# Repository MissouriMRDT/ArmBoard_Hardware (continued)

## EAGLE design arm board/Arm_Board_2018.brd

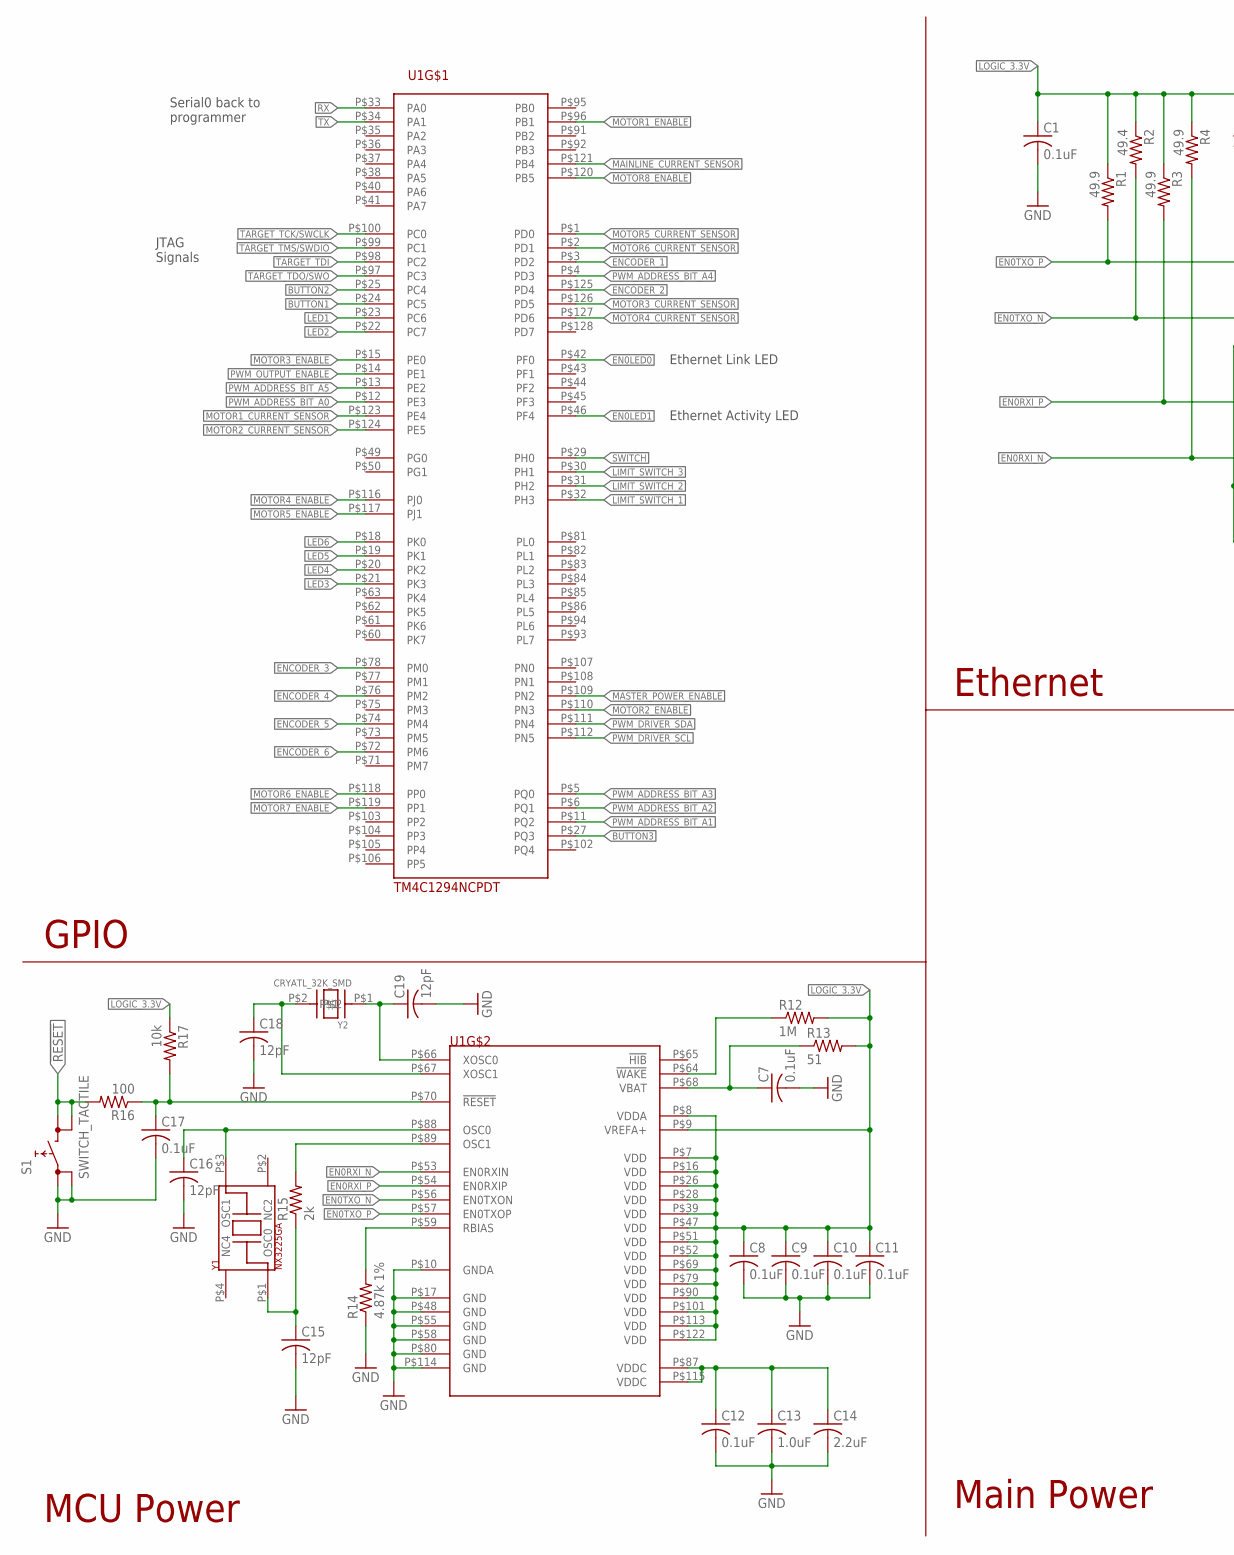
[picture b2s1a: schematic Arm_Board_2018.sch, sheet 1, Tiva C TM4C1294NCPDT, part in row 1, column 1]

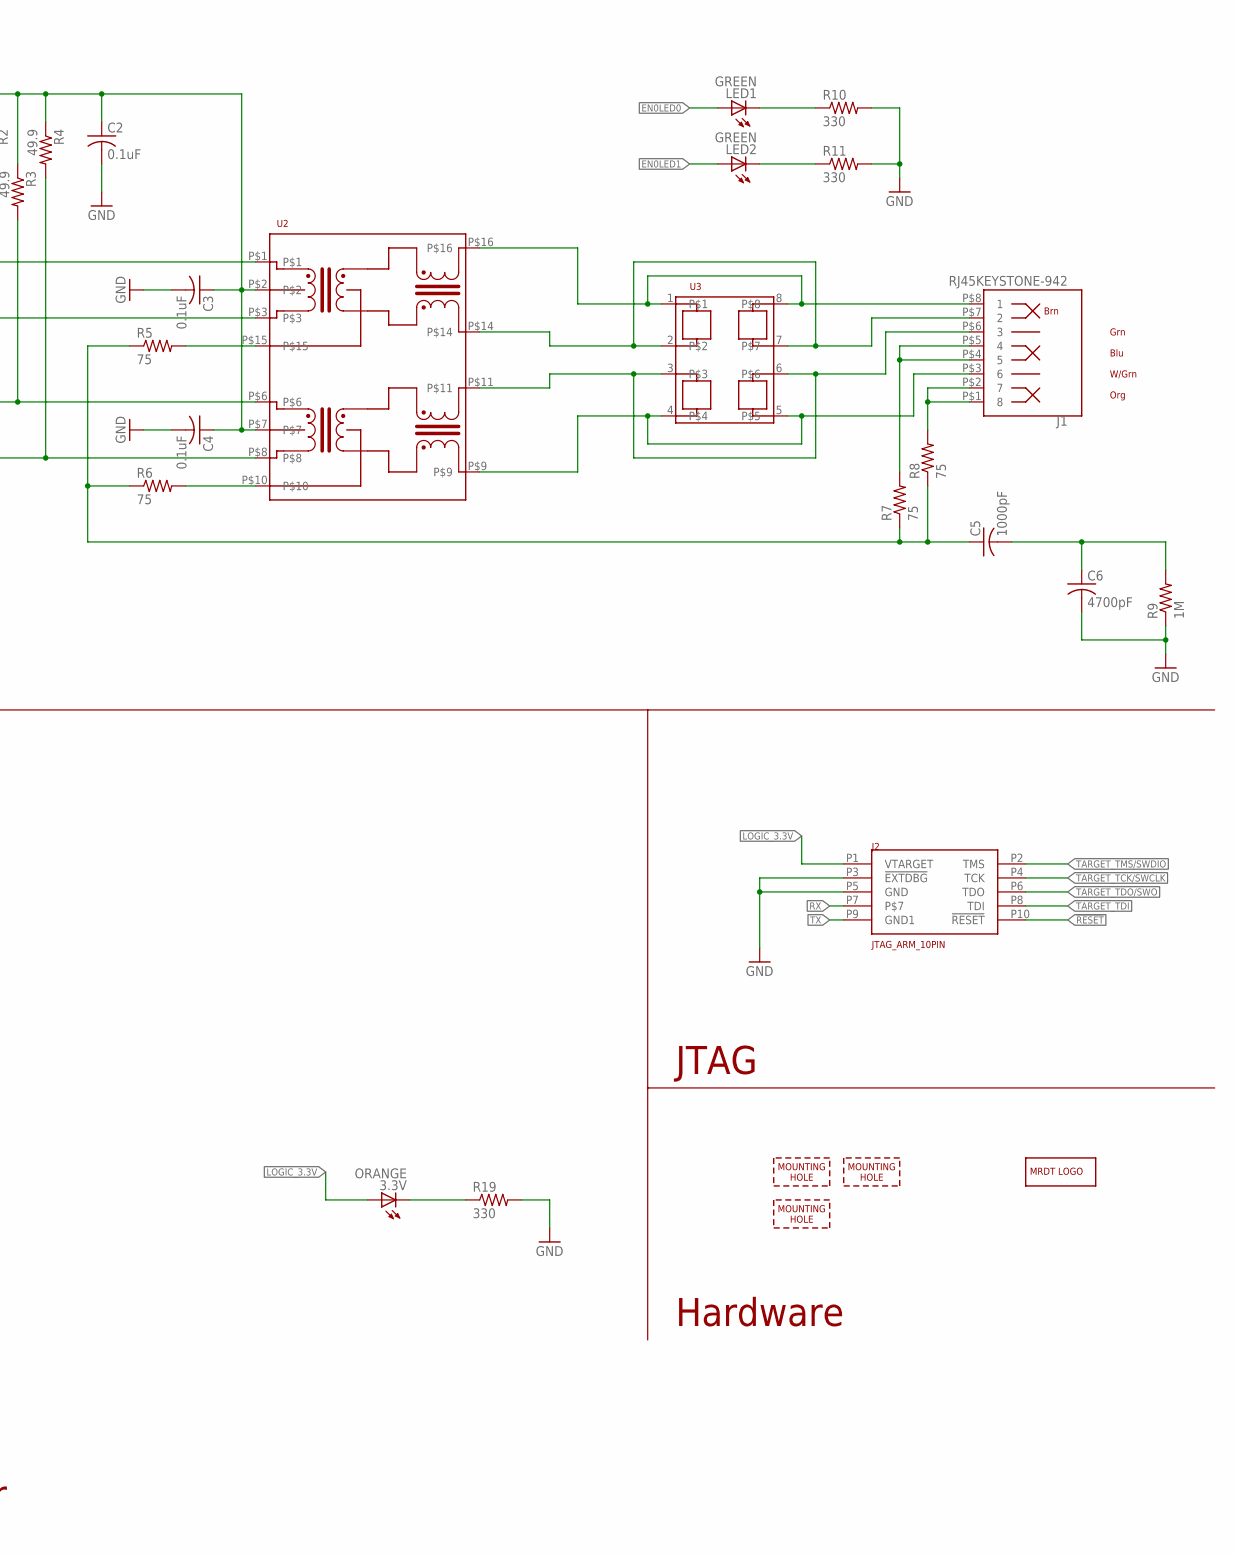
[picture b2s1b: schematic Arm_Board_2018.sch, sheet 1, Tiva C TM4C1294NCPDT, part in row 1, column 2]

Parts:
3.3V: ORANGE; CHIP-LED0603
C1, C2, C3, C4, C7, C8, C9, C10, C11, C12, C17: 0.1uF; C0603
C5: 1000pF; C0603
C6: 4700pF; C1206
C13: 1.0uF; C0603
C14: 2.2uF; C0603
C15, C16, C18, C19: 12pF; C0603
J1: RJ45KEYSTONE-942; KEYSTONE-942
J2: JTAG_ARM_10PIN; CON_2X5_50MIL
LED1, LED2: GREEN; CHIP-LED0603
R1, R3, R4: 49.9; R0603
R2: 49.4; R0603
R5, R6, R7, R8: 75; R0603
R9: 1M; R1206
R10, R11, R19: 330; R0603
R12: 1M; R0603
R13: 51; R0603
R14: 4.87k 1%; R0603
R15: 2k; R0603
R16: 100; R0603
R17: 10k; R0603
S1: SWITCH_TACTILE; SWITCH_6MM_6MM_TE_CON_SMD
U1: TM4C1294NCPDT; TQFP-128
U2: HX1198FNL
U3: SLVU2.8-4; SOIC8
U$1: MRDT_LOGO
U$2, U$3, U$4: MOUNTING_HOLE#6; #6_SCREW
Y1: NX3225GA; NDK3.2X2.5
Y2: CRYATL_32K_SMD; CRYSTAL_32K_SMD

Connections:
!RESET: J2.P10 (!RESET), R16.2, S1.P$3 (1), S1.P$4 (1)
BUTTON1: U1.P$24 (PC5); also elsewhere on the board
BUTTON2: U1.P$25 (PC4); also elsewhere on the board
BUTTON3: U1.P$27 (PQ3); also elsewhere on the board
EN0LED0: LED1.A, U1.P$42 (PF0)
EN0LED1: LED2.A, U1.P$46 (PF4)
EN0RXI_N: R4.2, U1.P$53 (EN0RXIN), U2.P$8
EN0RXI_P: R3.2, U1.P$54 (EN0RXIP), U2.P$6
EN0TXO_N: R2.2, U1.P$56 (EN0TXON), U2.P$3
EN0TXO_P: R1.2, U1.P$57 (EN0TXOP), U2.P$1
ENCODER_1: U1.P$3 (PD2); also elsewhere on the board
ENCODER_2: U1.P$125 (PD4); also elsewhere on the board
ENCODER_3: U1.P$78 (PM0); also elsewhere on the board
ENCODER_4: U1.P$76 (PM2); also elsewhere on the board
ENCODER_5: U1.P$74 (PM4); also elsewhere on the board
ENCODER_6: U1.P$72 (PM6); also elsewhere on the board
GND: C1.2, C2.2, C3.2, C4.2, C6.2, C7.2, C8.2, C9.2, C10.2, C11.2, C12.2, C13.2, C14.2, C15.2, C16.2, C17.2, C18.2, C19.2, J2.P3 (!EXTDBG), J2.P5 (GND), R9.1, R10.2, R11.2, R14.1, R19.2, S1.P$1 (0), S1.P$2 (0), U1.P$10 (GNDA), U1.P$17 (GND), U1.P$48 (GND), U1.P$55 (GND), U1.P$58 (GND), U1.P$80 (GND), U1.P$114 (GND); also elsewhere on the board
LED1: U1.P$23 (PC6); also elsewhere on the board
LED2: U1.P$22 (PC7); also elsewhere on the board
LED3: U1.P$21 (PK3); also elsewhere on the board
LED4: U1.P$20 (PK2); also elsewhere on the board
LED5: U1.P$19 (PK1); also elsewhere on the board
LED6: U1.P$18 (PK0); also elsewhere on the board
LIMIT_SWITCH_1: U1.P$32 (PH3); also elsewhere on the board
LIMIT_SWITCH_2: U1.P$31 (PH2); also elsewhere on the board
LIMIT_SWITCH_3: U1.P$30 (PH1); also elsewhere on the board
LOGIC_3.3V: 3.3V.A, C1.1, C2.1, C3.1, C4.1, C8.1, C9.1, C10.1, C11.1, J2.P1 (VTARGET), R1.1, R2.1, R3.1, R4.1, R12.2, R13.2, R17.1, U1.P$7 (VDD), U1.P$8 (VDDA), U1.P$9 (VREFA+), U1.P$16 (VDD), U1.P$26 (VDD), U1.P$28 (VDD), U1.P$39 (VDD), U1.P$47 (VDD), U1.P$51 (VDD), U1.P$52 (VDD), U1.P$69 (VDD), U1.P$79 (VDD), U1.P$90 (VDD), U1.P$101 (VDD), U1.P$113 (VDD), U1.P$122 (VDD), U2.P$2, U2.P$7; also elsewhere on the board
MAINLINE_CURRENT_SENSOR: U1.P$121 (PB4); also elsewhere on the board
MASTER_POWER_ENABLE: U1.P$109 (PN2); also elsewhere on the board
MOTOR1_CURRENT_SENSOR: U1.P$123 (PE4); also elsewhere on the board
MOTOR1_ENABLE: U1.P$96 (PB1); also elsewhere on the board
MOTOR2_CURRENT_SENSOR: U1.P$124 (PE5); also elsewhere on the board
MOTOR2_ENABLE: U1.P$110 (PN3); also elsewhere on the board
MOTOR3_CURRENT_SENSOR: U1.P$126 (PD5); also elsewhere on the board
MOTOR3_ENABLE: U1.P$15 (PE0); also elsewhere on the board
MOTOR4_CURRENT_SENSOR: U1.P$127 (PD6); also elsewhere on the board
MOTOR4_ENABLE: U1.P$116 (PJ0); also elsewhere on the board
MOTOR5_CURRENT_SENSOR: U1.P$1 (PD0); also elsewhere on the board
MOTOR5_ENABLE: U1.P$117 (PJ1); also elsewhere on the board
MOTOR6_CURRENT_SENSOR: U1.P$2 (PD1); also elsewhere on the board
MOTOR6_ENABLE: U1.P$118 (PP0); also elsewhere on the board
MOTOR7_ENABLE: U1.P$119 (PP1); also elsewhere on the board
MOTOR8_ENABLE: U1.P$120 (PB5); also elsewhere on the board
N_$1: R5.2, U2.P$15
N_$3: R6.2, U2.P$10
N_$4: J1.P$7 (2), U2.P$14, U3.2, U3.7
N_$5: J1.P$6 (3), U2.P$11, U3.3, U3.6
N_$6: J1.P$8 (1), U2.P$16, U3.1, U3.8
N_$7: J1.P$3 (6), U2.P$9, U3.4, U3.5
N_$8: LED2.C, R11.1
N_$9: LED1.C, R10.1
N_$10: C7.1, R13.1, U1.P$68 (VBAT)
N_$11: J1.P$4 (5), J1.P$5 (4), R7.2
N_$12: R12.1, U1.P$64 (!WAKE)
N_$13: J1.P$1 (8), J1.P$2 (7), R8.2
N_$14: C5.1, R5.1, R6.1, R7.1, R8.1
N_$15: C5.2, C6.1, R9.2
N_$16: C12.1, C13.1, C14.1, U1.P$87 (VDDC), U1.P$115 (VDDC)
N_$17: R15.2, U1.P$89 (OSC1)
N_$18: C16.1, U1.P$88 (OSC0), Y1.P$3 (OSC1)
N_$19: R14.2, U1.P$59 (RBIAS)
N_$20: C17.1, R16.1, R17.2, U1.P$70 (!RESET)
N_$21: C15.1, R15.1, Y1.P$1 (OSC0)
N_$22: C18.1, U1.P$67 (XOSC1), Y2.P$2
N_$23: C19.1, U1.P$66 (XOSC0), Y2.P$1
N_$26: 3.3V.C, R19.1
PWM_ADDRESS_BIT_A0: U1.P$12 (PE3)
PWM_ADDRESS_BIT_A1: U1.P$11 (PQ2)
PWM_ADDRESS_BIT_A2: U1.P$6 (PQ1)
PWM_ADDRESS_BIT_A3: U1.P$5 (PQ0)
PWM_ADDRESS_BIT_A4: U1.P$4 (PD3)
PWM_ADDRESS_BIT_A5: U1.P$13 (PE2)
PWM_DRIVER_SCL: U1.P$112 (PN5); also elsewhere on the board
PWM_DRIVER_SDA: U1.P$111 (PN4); also elsewhere on the board
PWM_OUTPUT_ENABLE: U1.P$14 (PE1); also elsewhere on the board
RX: J2.P7, U1.P$33 (PA0)
SWITCH: U1.P$29 (PH0); also elsewhere on the board
TARGET_TCK/SWCLK: J2.P4 (TCK), U1.P$100 (PC0)
TARGET_TDI: J2.P8 (TDI), U1.P$98 (PC2)
TARGET_TDO/SWO: J2.P6 (TDO), U1.P$97 (PC3)
TARGET_TMS/SWDIO: J2.P2 (TMS), U1.P$99 (PC1)
TX: J2.P9 (GND1), U1.P$34 (PA1)

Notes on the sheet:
Ethernet
GPIO
MCU Power
Main Power
JTAG
Hardware
Serial0 back to programmer
JTAG Signals
Ethernet Link LED
Ethernet Activity LED

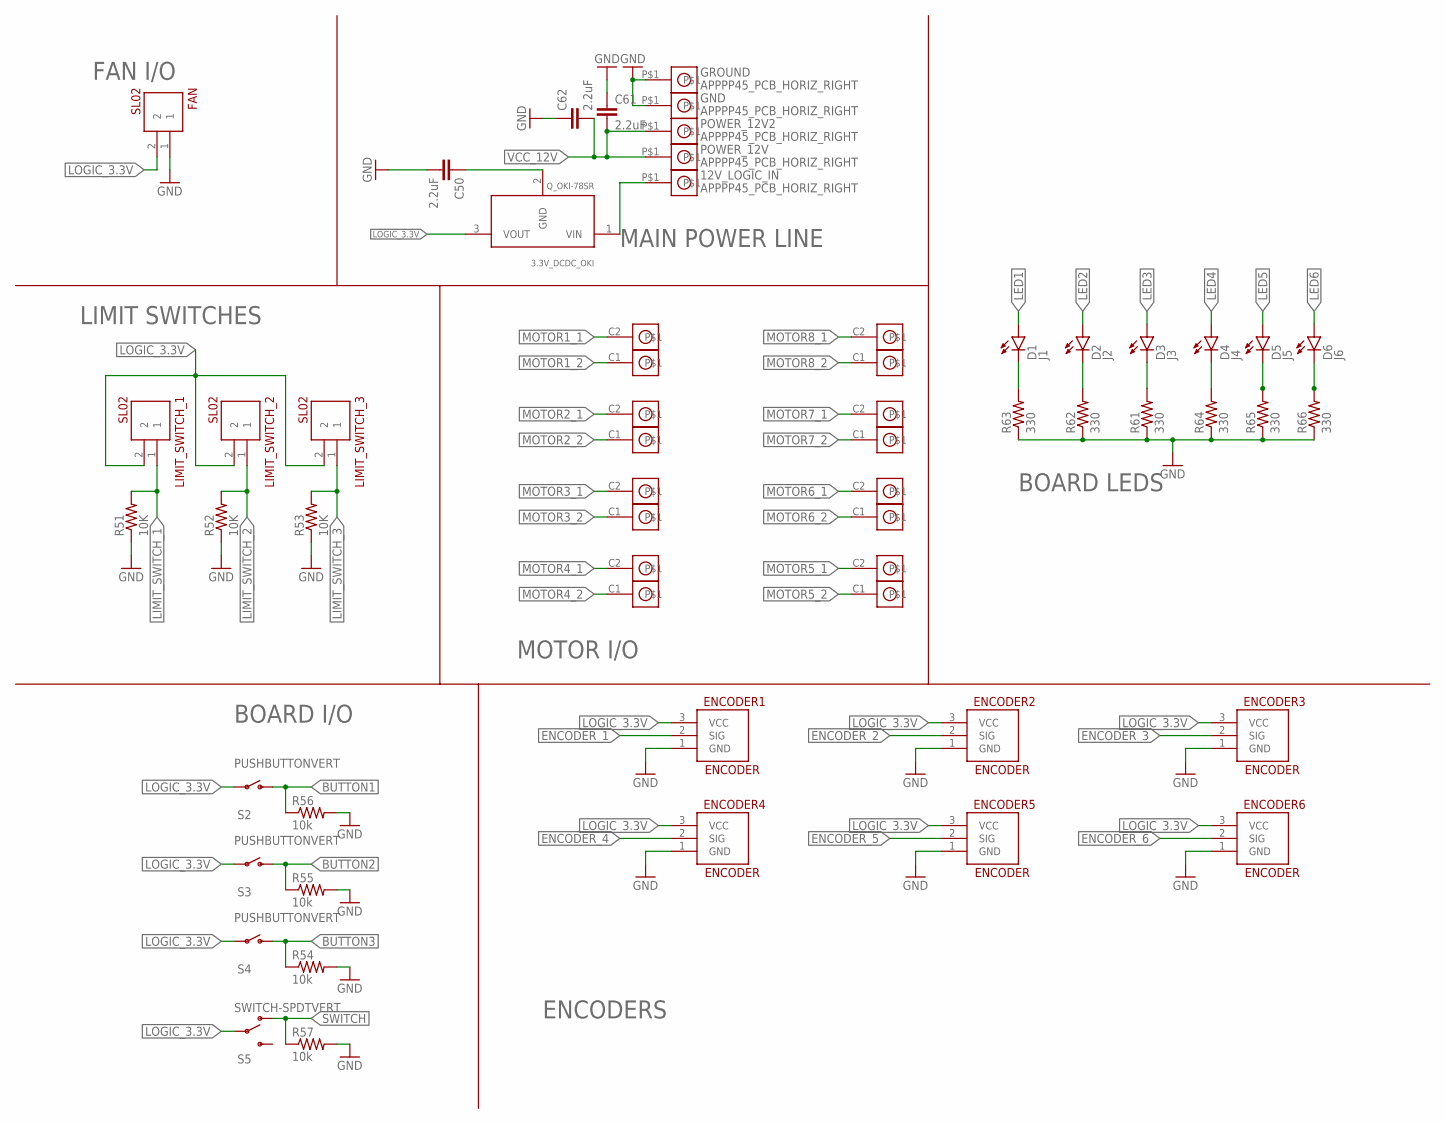
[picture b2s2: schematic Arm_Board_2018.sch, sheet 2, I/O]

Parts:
3.3V_DCDC_OKI: Q_OKI-78SR
12V_LOGIC_IN: APPPP45_PCB_HORIZ_RIGHT; APP45_PCB_HORIZ_RIGHT
C50: 2.2uF; 0603-CAP
C61, C62: 2.2uF; 1206
D1: J1; LED-0603
D2: J2; LED-0603
D3: J3; LED-0603
D4: J4; LED-0603
D5: J5; LED-0603
D6: J6; LED-0603
ENCODER1, ENCODER2, ENCODER3, ENCODER4, ENCODER5, ENCODER6: ENCODER; MOLEX-70543-0002
FAN: SL02; MOLEX-70543-0001
GND: APPPP45_PCB_HORIZ_RIGHT; APP45_PCB_HORIZ_RIGHT
GROUND: APPPP45_PCB_HORIZ_RIGHT; APP45_PCB_HORIZ_RIGHT
LIMIT_SWITCH_1, LIMIT_SWITCH_2, LIMIT_SWITCH_3: SL02; MOLEX-70543-0001
MOTOR1, MOTOR2, MOTOR3, MOTOR4, MOTOR5, MOTOR6, MOTOR7, MOTOR8: APP_2POS_CONFIGGENERAL_CONFIG; APP45_HORIZ_CONFIG
POWER_12V, POWER_12V2: APPPP45_PCB_HORIZ_RIGHT; APP45_PCB_HORIZ_RIGHT
R51, R52, R53: 10K; 0402-RES
R54, R55, R56, R57: 10k; 0402-RES
R61, R62, R63, R64, R65, R66: 330; 0402-RES
S2, S3, S4: PUSHBUTTONVERT; APEM-MJTP1243
S5: SWITCH-SPDTVERT; C&K-SS12D07VG4NSGAPA

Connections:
BUTTON1: R56.1, S2.P$2 (S); also elsewhere on the board
BUTTON2: R55.1, S3.P$2 (S); also elsewhere on the board
BUTTON3: R54.1, S4.P$2 (S); also elsewhere on the board
ENCODER_1: ENCODER1.2 (SIG); also elsewhere on the board
ENCODER_2: ENCODER2.2 (SIG); also elsewhere on the board
ENCODER_3: ENCODER3.2 (SIG); also elsewhere on the board
ENCODER_4: ENCODER4.2 (SIG); also elsewhere on the board
ENCODER_5: ENCODER5.2 (SIG); also elsewhere on the board
ENCODER_6: ENCODER6.2 (SIG); also elsewhere on the board
GND: C50.2, C61.1, C62.1, ENCODER1.1 (GND), ENCODER2.1 (GND), ENCODER3.1 (GND), ENCODER4.1 (GND), ENCODER5.1 (GND), ENCODER6.1 (GND), FAN.1, GND.P$1, GROUND.P$1, R51.1, R52.1, R53.1, R54.2, R55.2, R56.2, R57.2, R61.1, R62.1, R63.1, R64.1, R65.1, R66.1; also elsewhere on the board
LED1: D1.A; also elsewhere on the board
LED2: D2.A; also elsewhere on the board
LED3: D3.A; also elsewhere on the board
LED4: D4.A; also elsewhere on the board
LED5: D5.A; also elsewhere on the board
LED6: D6.A; also elsewhere on the board
LIMIT_SWITCH_1: LIMIT_SWITCH_1.1, R51.2; also elsewhere on the board
LIMIT_SWITCH_2: LIMIT_SWITCH_2.1, R52.2; also elsewhere on the board
LIMIT_SWITCH_3: LIMIT_SWITCH_3.1, R53.2; also elsewhere on the board
LOGIC_3.3V: 3.3V_DCDC_OKI.3 (VOUT), ENCODER1.3 (VCC), ENCODER2.3 (VCC), ENCODER3.3 (VCC), ENCODER4.3 (VCC), ENCODER5.3 (VCC), ENCODER6.3 (VCC), FAN.2, LIMIT_SWITCH_1.2, LIMIT_SWITCH_2.2, LIMIT_SWITCH_3.2, S2.P$1, S3.P$1, S4.P$1, S5.P$2; also elsewhere on the board
MOTOR1_1: MOTOR1.C2; also elsewhere on the board
MOTOR1_2: MOTOR1.C1; also elsewhere on the board
MOTOR2_1: MOTOR2.C2; also elsewhere on the board
MOTOR2_2: MOTOR2.C1; also elsewhere on the board
MOTOR3_1: MOTOR3.C2; also elsewhere on the board
MOTOR3_2: MOTOR3.C1; also elsewhere on the board
MOTOR4_1: MOTOR4.C2; also elsewhere on the board
MOTOR4_2: MOTOR4.C1; also elsewhere on the board
MOTOR5_1: MOTOR5.C2; also elsewhere on the board
MOTOR5_2: MOTOR5.C1; also elsewhere on the board
MOTOR6_1: MOTOR6.C2; also elsewhere on the board
MOTOR6_2: MOTOR6.C1; also elsewhere on the board
MOTOR7_1: MOTOR7.C2; also elsewhere on the board
MOTOR7_2: MOTOR7.C1; also elsewhere on the board
MOTOR8_1: MOTOR8.C2; also elsewhere on the board
MOTOR8_2: MOTOR8.C1; also elsewhere on the board
unnamed: 3.3V_DCDC_OKI.2 (GND), C50.1
unnamed: 3.3V_DCDC_OKI.1 (VIN), 12V_LOGIC_IN.P$1
unnamed: D1.C, R63.2
unnamed: D2.C, R62.2
unnamed: D6.C, R66.2
unnamed: D3.C, R61.2
unnamed: D4.C, R64.2
unnamed: D5.C, R65.2
SWITCH: R57.1, S5.P$3 (O); also elsewhere on the board
VCC_12V: C61.2, C62.2, POWER_12V.P$1, POWER_12V2.P$1; also elsewhere on the board

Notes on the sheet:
FAN I/O
MOTOR I/O
MAIN POWER LINE
LIMIT SWITCHES
ENCODERS
BOARD I/O
BOARD LEDS

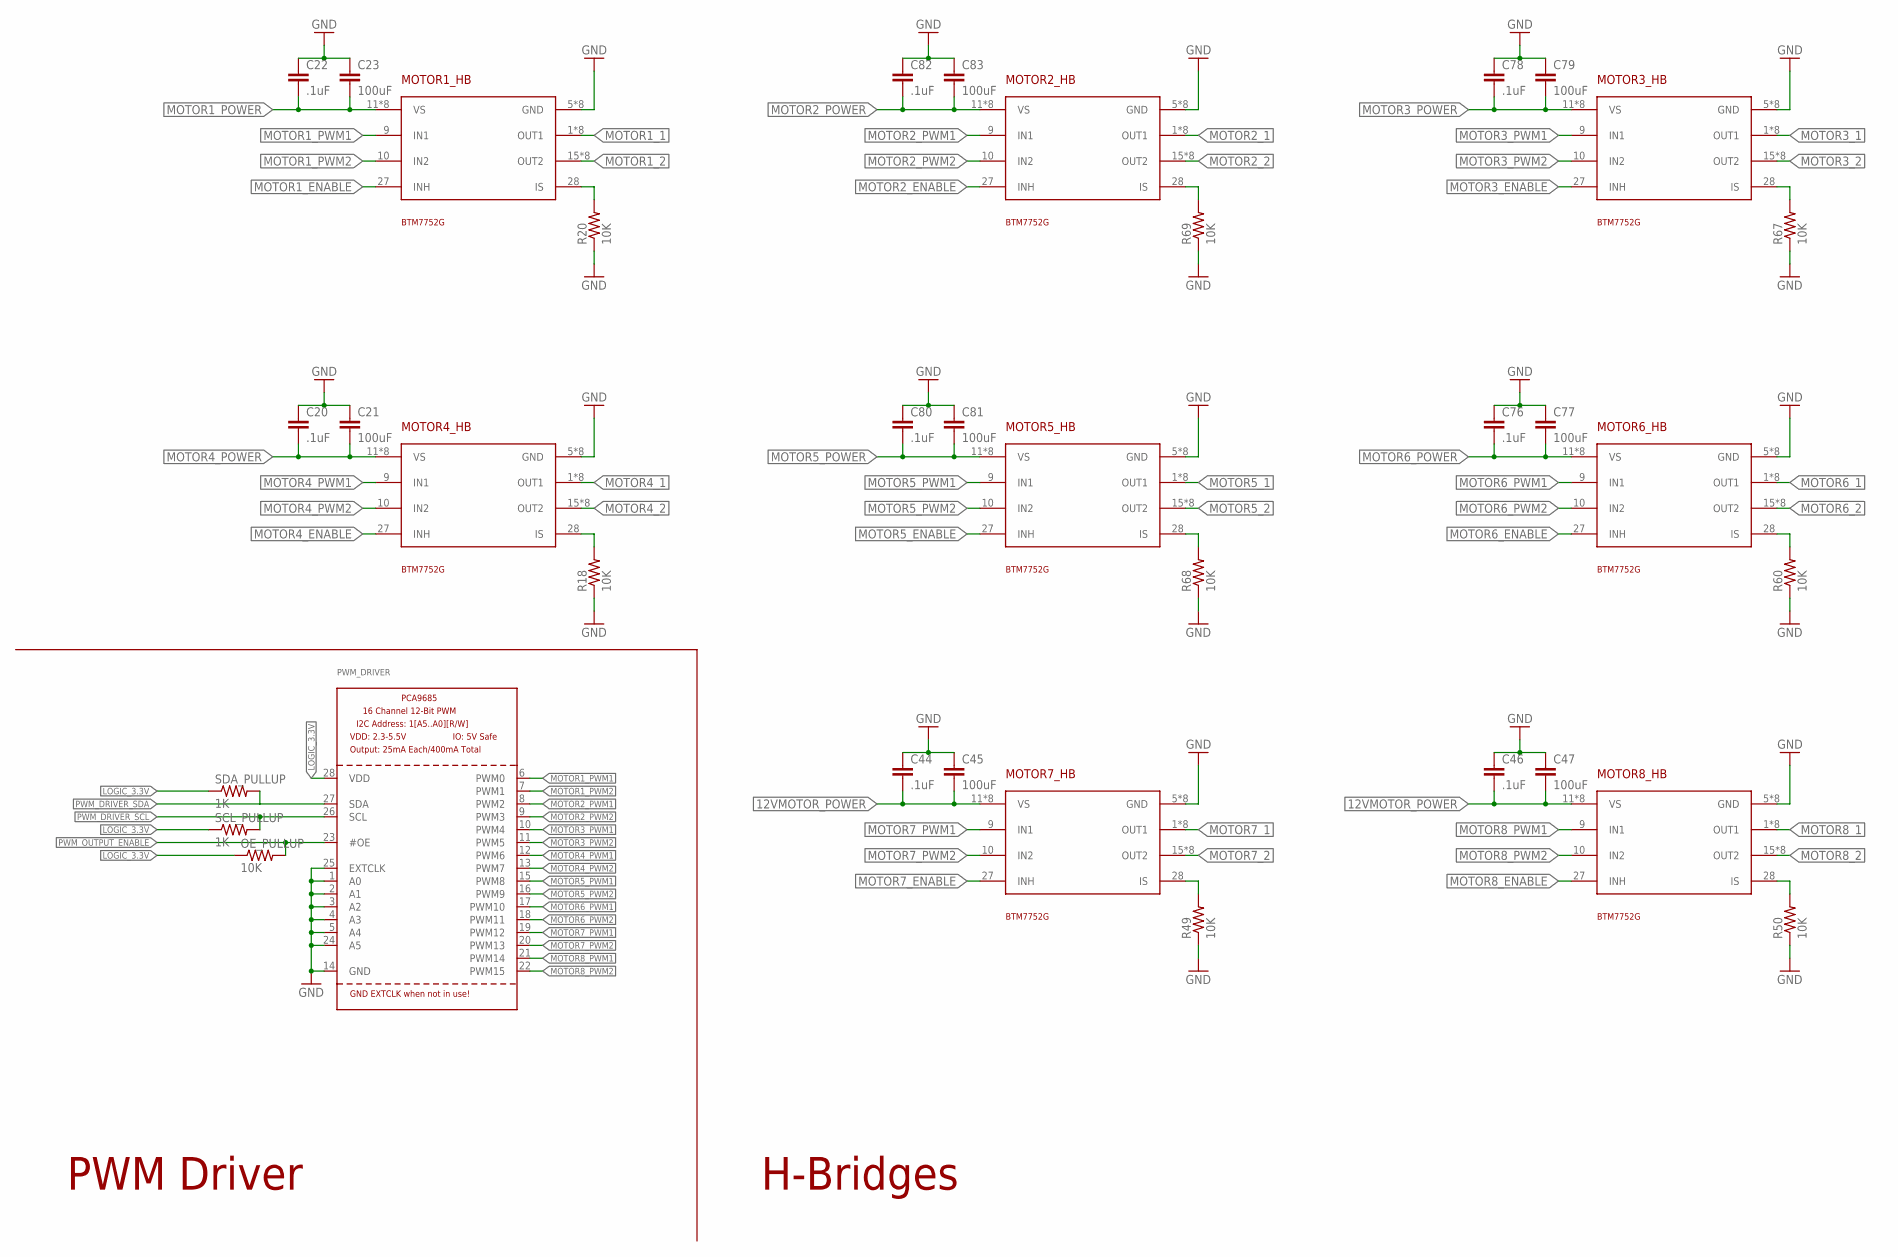
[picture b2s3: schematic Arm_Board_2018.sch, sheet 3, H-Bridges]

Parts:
C20, C22, C44, C46, C76, C78, C80, C82: .1uF; 0603-CAP
C21, C23, C45, C47, C77, C79, C81, C83: 100uF; 1210
MOTOR1_HB, MOTOR2_HB, MOTOR3_HB, MOTOR4_HB, MOTOR5_HB, MOTOR6_HB, MOTOR7_HB, MOTOR8_HB: BTM7752G; 36-BSSOP
OE_PULLUP: 10K; 0402-RES
PWM_DRIVER: PCA9685; TSSOP28
R18, R20, R49, R50, R60, R67, R68, R69: 10K; 0402-RES
SCL_PULLUP: 1K; 0402-RES
SDA_PULLUP: 1K; 0402-RES

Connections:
12VMOTOR_POWER: C44.2, C45.2, C46.2, C47.2, MOTOR7_HB.11 (VS), MOTOR7_HB.12 (VS), MOTOR7_HB.13 (VS), MOTOR7_HB.14 (VS), MOTOR7_HB.29 (VS), MOTOR7_HB.30 (VS), MOTOR7_HB.31 (VS), MOTOR7_HB.32 (VS), MOTOR8_HB.11 (VS), MOTOR8_HB.12 (VS), MOTOR8_HB.13 (VS), MOTOR8_HB.14 (VS), MOTOR8_HB.29 (VS), MOTOR8_HB.30 (VS), MOTOR8_HB.31 (VS), MOTOR8_HB.32 (VS); also elsewhere on the board
GND: C20.1, C21.1, C22.1, C23.1, C44.1, C45.1, C46.1, C47.1, C76.1, C77.1, C78.1, C79.1, C80.1, C81.1, C82.1, C83.1, MOTOR1_HB.5 (GND), MOTOR1_HB.6 (GND), MOTOR1_HB.7 (GND), MOTOR1_HB.8 (GND), MOTOR1_HB.23 (GND), MOTOR1_HB.24 (GND), MOTOR1_HB.25 (GND), MOTOR1_HB.26 (GND), MOTOR2_HB.5 (GND), MOTOR2_HB.6 (GND), MOTOR2_HB.7 (GND), MOTOR2_HB.8 (GND), MOTOR2_HB.23 (GND), MOTOR2_HB.24 (GND), MOTOR2_HB.25 (GND), MOTOR2_HB.26 (GND), MOTOR3_HB.5 (GND), MOTOR3_HB.6 (GND), MOTOR3_HB.7 (GND), MOTOR3_HB.8 (GND), MOTOR3_HB.23 (GND), MOTOR3_HB.24 (GND), MOTOR3_HB.25 (GND), MOTOR3_HB.26 (GND), MOTOR4_HB.5 (GND), MOTOR4_HB.6 (GND), MOTOR4_HB.7 (GND), MOTOR4_HB.8 (GND), MOTOR4_HB.23 (GND), MOTOR4_HB.24 (GND), MOTOR4_HB.25 (GND), MOTOR4_HB.26 (GND), MOTOR5_HB.5 (GND), MOTOR5_HB.6 (GND), MOTOR5_HB.7 (GND), MOTOR5_HB.8 (GND), MOTOR5_HB.23 (GND), MOTOR5_HB.24 (GND), MOTOR5_HB.25 (GND), MOTOR5_HB.26 (GND), MOTOR6_HB.5 (GND), MOTOR6_HB.6 (GND), MOTOR6_HB.7 (GND), MOTOR6_HB.8 (GND), MOTOR6_HB.23 (GND), MOTOR6_HB.24 (GND), MOTOR6_HB.25 (GND), MOTOR6_HB.26 (GND), MOTOR7_HB.5 (GND), MOTOR7_HB.6 (GND), MOTOR7_HB.7 (GND), MOTOR7_HB.8 (GND), MOTOR7_HB.23 (GND), MOTOR7_HB.24 (GND), MOTOR7_HB.25 (GND), MOTOR7_HB.26 (GND), MOTOR8_HB.5 (GND), MOTOR8_HB.6 (GND), MOTOR8_HB.7 (GND), MOTOR8_HB.8 (GND), MOTOR8_HB.23 (GND), MOTOR8_HB.24 (GND), MOTOR8_HB.25 (GND), MOTOR8_HB.26 (GND), PWM_DRIVER.1 (A0), PWM_DRIVER.2 (A1), PWM_DRIVER.3 (A2), PWM_DRIVER.4 (A3), PWM_DRIVER.5 (A4), PWM_DRIVER.14 (GND), PWM_DRIVER.24 (A5), PWM_DRIVER.25 (EXTCLK), R18.1, R20.1, R49.1, R50.1, R60.1, R67.1, R68.1, R69.1; also elsewhere on the board
LOGIC_3.3V: OE_PULLUP.1, PWM_DRIVER.28 (VDD), SCL_PULLUP.1, SDA_PULLUP.1; also elsewhere on the board
MOTOR1_1: MOTOR1_HB.1 (OUT1), MOTOR1_HB.2 (OUT1), MOTOR1_HB.3 (OUT1), MOTOR1_HB.4 (OUT1), MOTOR1_HB.33 (OUT1), MOTOR1_HB.34 (OUT1), MOTOR1_HB.35 (OUT1), MOTOR1_HB.36 (OUT1); also elsewhere on the board
MOTOR1_2: MOTOR1_HB.15 (OUT2), MOTOR1_HB.16 (OUT2), MOTOR1_HB.17 (OUT2), MOTOR1_HB.18 (OUT2), MOTOR1_HB.19 (OUT2), MOTOR1_HB.20 (OUT2), MOTOR1_HB.21 (OUT2), MOTOR1_HB.22 (OUT2); also elsewhere on the board
MOTOR1_ENABLE: MOTOR1_HB.27 (INH); also elsewhere on the board
MOTOR1_POWER: C22.2, C23.2, MOTOR1_HB.11 (VS), MOTOR1_HB.12 (VS), MOTOR1_HB.13 (VS), MOTOR1_HB.14 (VS), MOTOR1_HB.29 (VS), MOTOR1_HB.30 (VS), MOTOR1_HB.31 (VS), MOTOR1_HB.32 (VS); also elsewhere on the board
MOTOR1_PWM1: MOTOR1_HB.9 (IN1), PWM_DRIVER.6 (PWM0)
MOTOR1_PWM2: MOTOR1_HB.10 (IN2), PWM_DRIVER.7 (PWM1)
MOTOR2_1: MOTOR2_HB.1 (OUT1), MOTOR2_HB.2 (OUT1), MOTOR2_HB.3 (OUT1), MOTOR2_HB.4 (OUT1), MOTOR2_HB.33 (OUT1), MOTOR2_HB.34 (OUT1), MOTOR2_HB.35 (OUT1), MOTOR2_HB.36 (OUT1); also elsewhere on the board
MOTOR2_2: MOTOR2_HB.15 (OUT2), MOTOR2_HB.16 (OUT2), MOTOR2_HB.17 (OUT2), MOTOR2_HB.18 (OUT2), MOTOR2_HB.19 (OUT2), MOTOR2_HB.20 (OUT2), MOTOR2_HB.21 (OUT2), MOTOR2_HB.22 (OUT2); also elsewhere on the board
MOTOR2_ENABLE: MOTOR2_HB.27 (INH); also elsewhere on the board
MOTOR2_POWER: C82.2, C83.2, MOTOR2_HB.11 (VS), MOTOR2_HB.12 (VS), MOTOR2_HB.13 (VS), MOTOR2_HB.14 (VS), MOTOR2_HB.29 (VS), MOTOR2_HB.30 (VS), MOTOR2_HB.31 (VS), MOTOR2_HB.32 (VS); also elsewhere on the board
MOTOR2_PWM1: MOTOR2_HB.9 (IN1), PWM_DRIVER.8 (PWM2)
MOTOR2_PWM2: MOTOR2_HB.10 (IN2), PWM_DRIVER.9 (PWM3)
MOTOR3_1: MOTOR3_HB.1 (OUT1), MOTOR3_HB.2 (OUT1), MOTOR3_HB.3 (OUT1), MOTOR3_HB.4 (OUT1), MOTOR3_HB.33 (OUT1), MOTOR3_HB.34 (OUT1), MOTOR3_HB.35 (OUT1), MOTOR3_HB.36 (OUT1); also elsewhere on the board
MOTOR3_2: MOTOR3_HB.15 (OUT2), MOTOR3_HB.16 (OUT2), MOTOR3_HB.17 (OUT2), MOTOR3_HB.18 (OUT2), MOTOR3_HB.19 (OUT2), MOTOR3_HB.20 (OUT2), MOTOR3_HB.21 (OUT2), MOTOR3_HB.22 (OUT2); also elsewhere on the board
MOTOR3_ENABLE: MOTOR3_HB.27 (INH); also elsewhere on the board
MOTOR3_POWER: C78.2, C79.2, MOTOR3_HB.11 (VS), MOTOR3_HB.12 (VS), MOTOR3_HB.13 (VS), MOTOR3_HB.14 (VS), MOTOR3_HB.29 (VS), MOTOR3_HB.30 (VS), MOTOR3_HB.31 (VS), MOTOR3_HB.32 (VS); also elsewhere on the board
MOTOR3_PWM1: MOTOR3_HB.9 (IN1), PWM_DRIVER.10 (PWM4)
MOTOR3_PWM2: MOTOR3_HB.10 (IN2), PWM_DRIVER.11 (PWM5)
MOTOR4_1: MOTOR4_HB.1 (OUT1), MOTOR4_HB.2 (OUT1), MOTOR4_HB.3 (OUT1), MOTOR4_HB.4 (OUT1), MOTOR4_HB.33 (OUT1), MOTOR4_HB.34 (OUT1), MOTOR4_HB.35 (OUT1), MOTOR4_HB.36 (OUT1); also elsewhere on the board
MOTOR4_2: MOTOR4_HB.15 (OUT2), MOTOR4_HB.16 (OUT2), MOTOR4_HB.17 (OUT2), MOTOR4_HB.18 (OUT2), MOTOR4_HB.19 (OUT2), MOTOR4_HB.20 (OUT2), MOTOR4_HB.21 (OUT2), MOTOR4_HB.22 (OUT2); also elsewhere on the board
MOTOR4_ENABLE: MOTOR4_HB.27 (INH); also elsewhere on the board
MOTOR4_POWER: C20.2, C21.2, MOTOR4_HB.11 (VS), MOTOR4_HB.12 (VS), MOTOR4_HB.13 (VS), MOTOR4_HB.14 (VS), MOTOR4_HB.29 (VS), MOTOR4_HB.30 (VS), MOTOR4_HB.31 (VS), MOTOR4_HB.32 (VS); also elsewhere on the board
MOTOR4_PWM1: MOTOR4_HB.9 (IN1), PWM_DRIVER.12 (PWM6)
MOTOR4_PWM2: MOTOR4_HB.10 (IN2), PWM_DRIVER.13 (PWM7)
MOTOR5_1: MOTOR5_HB.1 (OUT1), MOTOR5_HB.2 (OUT1), MOTOR5_HB.3 (OUT1), MOTOR5_HB.4 (OUT1), MOTOR5_HB.33 (OUT1), MOTOR5_HB.34 (OUT1), MOTOR5_HB.35 (OUT1), MOTOR5_HB.36 (OUT1); also elsewhere on the board
MOTOR5_2: MOTOR5_HB.15 (OUT2), MOTOR5_HB.16 (OUT2), MOTOR5_HB.17 (OUT2), MOTOR5_HB.18 (OUT2), MOTOR5_HB.19 (OUT2), MOTOR5_HB.20 (OUT2), MOTOR5_HB.21 (OUT2), MOTOR5_HB.22 (OUT2); also elsewhere on the board
MOTOR5_ENABLE: MOTOR5_HB.27 (INH); also elsewhere on the board
MOTOR5_POWER: C80.2, C81.2, MOTOR5_HB.11 (VS), MOTOR5_HB.12 (VS), MOTOR5_HB.13 (VS), MOTOR5_HB.14 (VS), MOTOR5_HB.29 (VS), MOTOR5_HB.30 (VS), MOTOR5_HB.31 (VS), MOTOR5_HB.32 (VS); also elsewhere on the board
MOTOR5_PWM1: MOTOR5_HB.9 (IN1), PWM_DRIVER.15 (PWM8)
MOTOR5_PWM2: MOTOR5_HB.10 (IN2), PWM_DRIVER.16 (PWM9)
MOTOR6_1: MOTOR6_HB.1 (OUT1), MOTOR6_HB.2 (OUT1), MOTOR6_HB.3 (OUT1), MOTOR6_HB.4 (OUT1), MOTOR6_HB.33 (OUT1), MOTOR6_HB.34 (OUT1), MOTOR6_HB.35 (OUT1), MOTOR6_HB.36 (OUT1); also elsewhere on the board
MOTOR6_2: MOTOR6_HB.15 (OUT2), MOTOR6_HB.16 (OUT2), MOTOR6_HB.17 (OUT2), MOTOR6_HB.18 (OUT2), MOTOR6_HB.19 (OUT2), MOTOR6_HB.20 (OUT2), MOTOR6_HB.21 (OUT2), MOTOR6_HB.22 (OUT2); also elsewhere on the board
MOTOR6_ENABLE: MOTOR6_HB.27 (INH); also elsewhere on the board
MOTOR6_POWER: C76.2, C77.2, MOTOR6_HB.11 (VS), MOTOR6_HB.12 (VS), MOTOR6_HB.13 (VS), MOTOR6_HB.14 (VS), MOTOR6_HB.29 (VS), MOTOR6_HB.30 (VS), MOTOR6_HB.31 (VS), MOTOR6_HB.32 (VS); also elsewhere on the board
MOTOR6_PWM1: MOTOR6_HB.9 (IN1), PWM_DRIVER.17 (PWM10)
MOTOR6_PWM2: MOTOR6_HB.10 (IN2), PWM_DRIVER.18 (PWM11)
MOTOR7_1: MOTOR7_HB.1 (OUT1), MOTOR7_HB.2 (OUT1), MOTOR7_HB.3 (OUT1), MOTOR7_HB.4 (OUT1), MOTOR7_HB.33 (OUT1), MOTOR7_HB.34 (OUT1), MOTOR7_HB.35 (OUT1), MOTOR7_HB.36 (OUT1); also elsewhere on the board
MOTOR7_2: MOTOR7_HB.15 (OUT2), MOTOR7_HB.16 (OUT2), MOTOR7_HB.17 (OUT2), MOTOR7_HB.18 (OUT2), MOTOR7_HB.19 (OUT2), MOTOR7_HB.20 (OUT2), MOTOR7_HB.21 (OUT2), MOTOR7_HB.22 (OUT2); also elsewhere on the board
MOTOR7_ENABLE: MOTOR7_HB.27 (INH); also elsewhere on the board
MOTOR7_PWM1: MOTOR7_HB.9 (IN1), PWM_DRIVER.19 (PWM12)
MOTOR7_PWM2: MOTOR7_HB.10 (IN2), PWM_DRIVER.20 (PWM13)
MOTOR8_1: MOTOR8_HB.1 (OUT1), MOTOR8_HB.2 (OUT1), MOTOR8_HB.3 (OUT1), MOTOR8_HB.4 (OUT1), MOTOR8_HB.33 (OUT1), MOTOR8_HB.34 (OUT1), MOTOR8_HB.35 (OUT1), MOTOR8_HB.36 (OUT1); also elsewhere on the board
MOTOR8_2: MOTOR8_HB.15 (OUT2), MOTOR8_HB.16 (OUT2), MOTOR8_HB.17 (OUT2), MOTOR8_HB.18 (OUT2), MOTOR8_HB.19 (OUT2), MOTOR8_HB.20 (OUT2), MOTOR8_HB.21 (OUT2), MOTOR8_HB.22 (OUT2); also elsewhere on the board
MOTOR8_ENABLE: MOTOR8_HB.27 (INH); also elsewhere on the board
MOTOR8_PWM1: MOTOR8_HB.9 (IN1), PWM_DRIVER.21 (PWM14)
MOTOR8_PWM2: MOTOR8_HB.10 (IN2), PWM_DRIVER.22 (PWM15)
unnamed: MOTOR4_HB.28 (IS), R18.2
unnamed: MOTOR1_HB.28 (IS), R20.2
unnamed: MOTOR6_HB.28 (IS), R60.2
unnamed: MOTOR3_HB.28 (IS), R67.2
unnamed: MOTOR8_HB.28 (IS), R50.2
unnamed: MOTOR7_HB.28 (IS), R49.2
unnamed: MOTOR5_HB.28 (IS), R68.2
unnamed: MOTOR2_HB.28 (IS), R69.2
PWM_DRIVER_SCL: PWM_DRIVER.26 (SCL), SCL_PULLUP.2; also elsewhere on the board
PWM_DRIVER_SDA: PWM_DRIVER.27 (SDA), SDA_PULLUP.2; also elsewhere on the board
PWM_OUTPUT_ENABLE: OE_PULLUP.2, PWM_DRIVER.23 (#OE); also elsewhere on the board

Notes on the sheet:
PWM Driver
H-Bridges

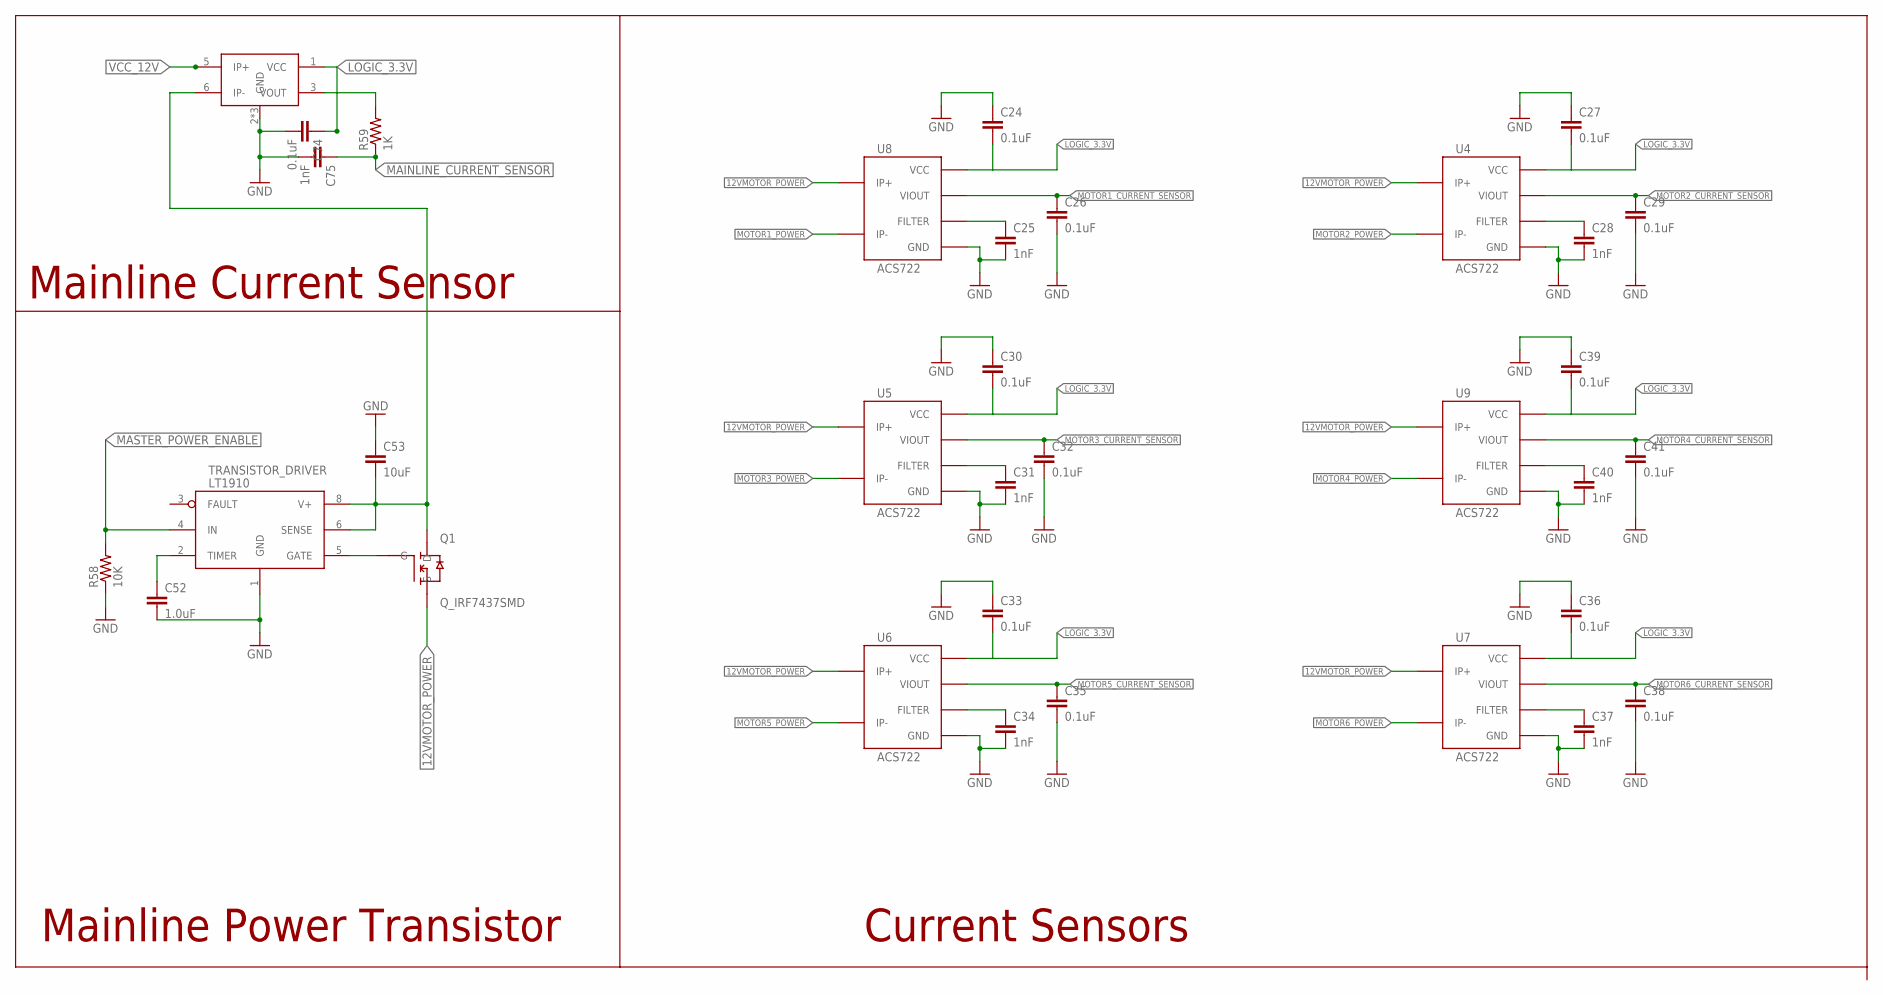
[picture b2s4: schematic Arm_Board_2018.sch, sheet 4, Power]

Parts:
C24, C26, C27, C29, C30, C32, C33, C35, C36, C38, C39, C41, C74: 0.1uF; 0603-CAP
C25, C28, C31, C34, C37, C40, C75: 1nF; 0603-CAP
C52: 1.0uF; 0603-CAP
C53: 10uF; 0603-CAP
MAINLINE_CURRENT: ACS781; 7-POWER_SMD_MODULE
Q1: Q_IRF7437SMD; D2PACK
R58: 10K; 0402-RES
R59: 1K; 0402-RES
TRANSISTOR_DRIVER: LT1910; SO8
U4, U5, U6, U7, U8, U9: ACS722; SOIC8

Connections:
12VMOTOR_POWER: Q1.2 (S), U4.1 (IP+), U4.2 (IP+), U5.1 (IP+), U5.2 (IP+), U6.1 (IP+), U6.2 (IP+), U7.1 (IP+), U7.2 (IP+), U8.1 (IP+), U8.2 (IP+), U9.1 (IP+), U9.2 (IP+); also elsewhere on the board
GND: C24.1, C25.2, C26.2, C27.1, C28.2, C29.2, C30.1, C31.2, C32.2, C33.1, C34.2, C35.2, C36.1, C37.2, C38.2, C39.1, C40.2, C41.2, C52.2, C53.1, C74.2, C75.2, MAINLINE_CURRENT.2 (GND), MAINLINE_CURRENT.4 (GND), MAINLINE_CURRENT.7 (GND), R58.1, TRANSISTOR_DRIVER.1 (GND), U4.5 (GND), U5.5 (GND), U6.5 (GND), U7.5 (GND), U8.5 (GND), U9.5 (GND); also elsewhere on the board
LOGIC_3.3V: C24.2, C27.2, C30.2, C33.2, C36.2, C39.2, C74.1, MAINLINE_CURRENT.1 (VCC), U4.8 (VCC), U5.8 (VCC), U6.8 (VCC), U7.8 (VCC), U8.8 (VCC), U9.8 (VCC); also elsewhere on the board
MAINLINE_CURRENT_SENSOR: C75.1, R59.1; also elsewhere on the board
MASTER_POWER_ENABLE: R58.2, TRANSISTOR_DRIVER.4 (IN); also elsewhere on the board
MOTOR1_CURRENT_SENSOR: C26.1, U8.7 (VIOUT); also elsewhere on the board
MOTOR1_POWER: U8.3 (IP-), U8.4 (IP-); also elsewhere on the board
MOTOR2_CURRENT_SENSOR: C29.1, U4.7 (VIOUT); also elsewhere on the board
MOTOR2_POWER: U4.3 (IP-), U4.4 (IP-); also elsewhere on the board
MOTOR3_CURRENT_SENSOR: C32.1, U5.7 (VIOUT); also elsewhere on the board
MOTOR3_POWER: U5.3 (IP-), U5.4 (IP-); also elsewhere on the board
MOTOR4_CURRENT_SENSOR: C41.1, U9.7 (VIOUT); also elsewhere on the board
MOTOR4_POWER: U9.3 (IP-), U9.4 (IP-); also elsewhere on the board
MOTOR5_CURRENT_SENSOR: C35.1, U6.7 (VIOUT); also elsewhere on the board
MOTOR5_POWER: U6.3 (IP-), U6.4 (IP-); also elsewhere on the board
MOTOR6_CURRENT_SENSOR: C38.1, U7.7 (VIOUT); also elsewhere on the board
MOTOR6_POWER: U7.3 (IP-), U7.4 (IP-); also elsewhere on the board
unnamed: C28.1, U4.6 (FILTER)
unnamed: C52.1, TRANSISTOR_DRIVER.2 (TIMER)
unnamed: C25.1, U8.6 (FILTER)
unnamed: C31.1, U5.6 (FILTER)
unnamed: C34.1, U6.6 (FILTER)
unnamed: C37.1, U7.6 (FILTER)
unnamed: C40.1, U9.6 (FILTER)
unnamed: Q1.1 (G), TRANSISTOR_DRIVER.5 (GATE)
unnamed: C53.2, MAINLINE_CURRENT.6 (IP-), Q1.TAB (D), TRANSISTOR_DRIVER.6 (SENSE), TRANSISTOR_DRIVER.8 (V+)
unnamed: MAINLINE_CURRENT.3 (VOUT), R59.2
VCC_12V: MAINLINE_CURRENT.5 (IP+); also elsewhere on the board

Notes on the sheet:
Current Sensors
Mainline Current Sensor
Mainline Power Transistor
